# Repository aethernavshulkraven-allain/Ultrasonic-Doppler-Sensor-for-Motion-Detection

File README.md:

# SonarProject

# Objective
The objective of the lab assignments – over the course of the semester – is to learn how to
(a) Design
(b) Simulate
(c) Fabricate and
(d) Test a narrowband ultrasonic Doppler sensor for motion detection.
# Skills Gained
(a) Learn how to read a datasheet and choose appropriate components for a design
(b) Learn how to draw a schematic
(c) Learn how to simulate the behavior of the circuit on LTSpice
(d) Do the PCB layout required for fabrication
(e) Solder components on the PCB
(f) Test the performance of the circuit and compare the performance with simulation results

# Description
The system level configuration of the ultrasonic narrow band Doppler sensor is shown in Figure.1. The
system consists of transmitter and receiver circuits. The transmitter consists of a crystal oscillator that
generates a 2MHz sinusoidal signal. The frequency divider divides the 2MHz signal by a factor of 50 to generate a 40KHz (fo) output signal. A low pass filter is used to remove any higher order harmonics that
may be generated. The filter may be designed as an active filter to provide voltage amplification to the
transmitted signal. The signal may be amplified and conveyed to the acoustic transducer where the
electrical signal is converted to acoustic signal and transmitted as shown in the equation below.

The received signal from a moving target consists of a Doppler shifted signal.

The received signal is much weaker than the transmitted signal (Arx < Atx). Hence, the signal is passed
through a low noise amplifier for voltage amplification. Then the signal is band pass filtered to remove
higher order harmonics and limit external interference. The signal is then captured in the oscilloscope. The
frequency domain of the received signal should show a shift in the frequency from 40KHz when a target
moves before the sonar. Note that when the hand is moving, the Doppler frequency shift may change with
time. Note that the sonar must be configured such that the strong transmitted signal does not directly leak
into the receiver. The transducers are typically very directional. So the sonar must be carefully configured
such that the transmitter and receiving transducers do not face each other and instead face the target.
While performing experiments with a moving target, please ensure that the target is within the field of view
of the sonar.

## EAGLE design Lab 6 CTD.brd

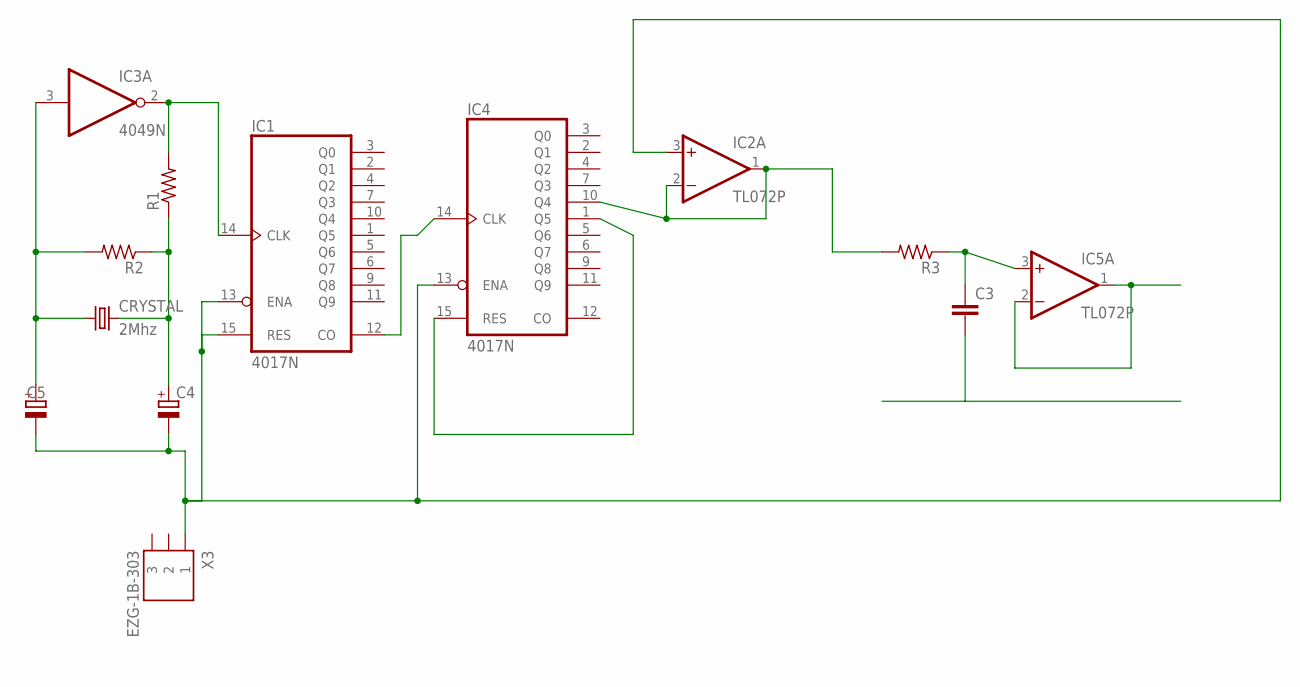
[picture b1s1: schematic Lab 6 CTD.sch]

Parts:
C3: C-EU050-025X075; C050-025X075
C4, C5: CPOL-EUB45181A; B45181A
CRYSTAL: 2Mhz; HC49U-V
IC1, IC4: 4017N; DIL16
IC2, IC5: TL072P; DIL08
IC3: 4049N; DIL16
R1, R2, R3: R-US_0411/15; 0411/15
X3: EZG-1B-303; EZG-1B-1K-303

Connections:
unnamed: IC1.14 (CLK), IC3.2 (O), R1.2
unnamed: IC1.12 (CO), IC4.14 (CLK)
unnamed: IC4.1 (Q5), IC4.15 (RES)
unnamed: C4.+, CRYSTAL.2, R1.1, R2.1
unnamed: C5.+, CRYSTAL.1, IC3.3 (I), R2.2
unnamed: IC2.1 (OUT), IC2.2 (-IN), IC4.10 (Q4), R3.2
unnamed: C3.1, IC5.3 (+IN), R3.1
unnamed: IC5.1 (OUT), IC5.2 (-IN)
unnamed: C4.-, C5.-, IC1.13 (ENA), IC1.15 (RES), IC2.3 (+IN), IC4.13 (ENA), X3.1
V+: IC2.8 (V+), IC5.8 (V+)
V-: IC2.4 (V-), IC5.4 (V-)
VDD: IC1.16 (VDD), IC3.1 (VDD), IC4.16 (VDD)
VSS: IC1.8 (VSS), IC3.8 (VSS), IC4.8 (VSS)

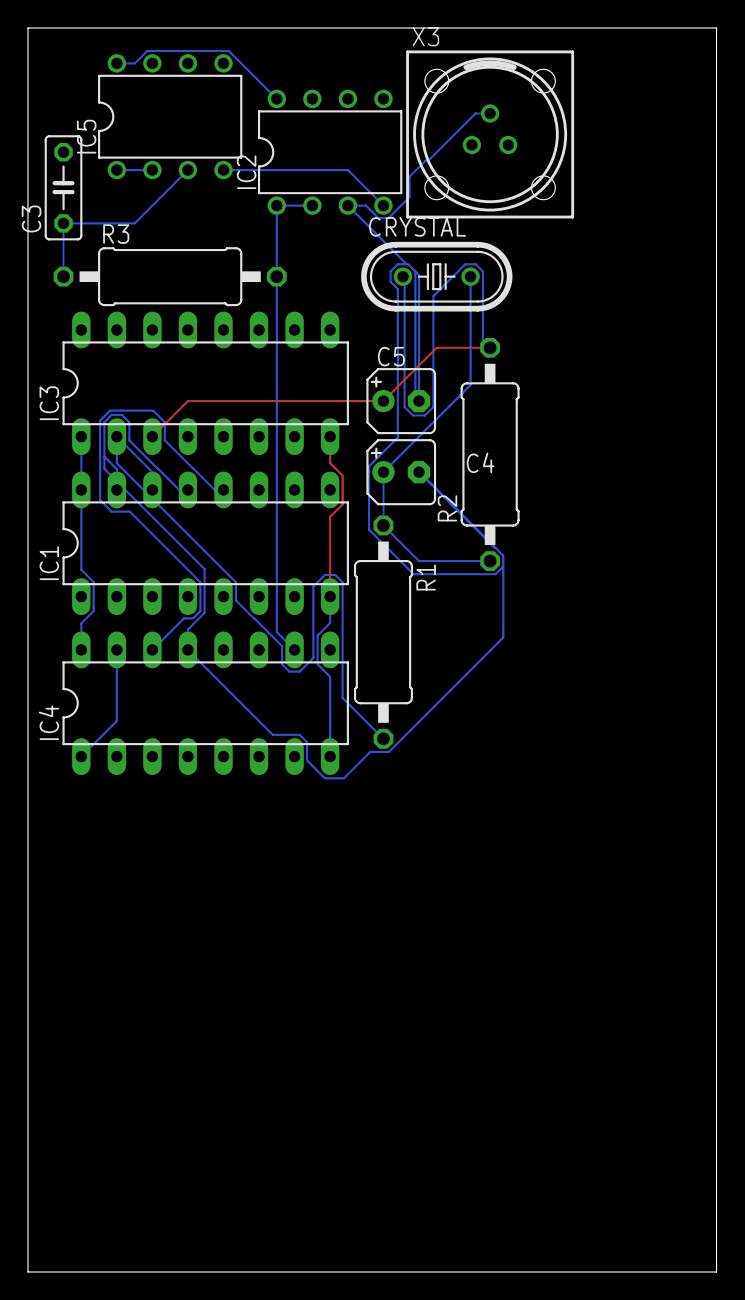
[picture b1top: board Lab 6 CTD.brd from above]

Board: 2 copper layers, 49.2 x 88.9 mm, 13 parts (0 on the bottom side), 13 nets.
